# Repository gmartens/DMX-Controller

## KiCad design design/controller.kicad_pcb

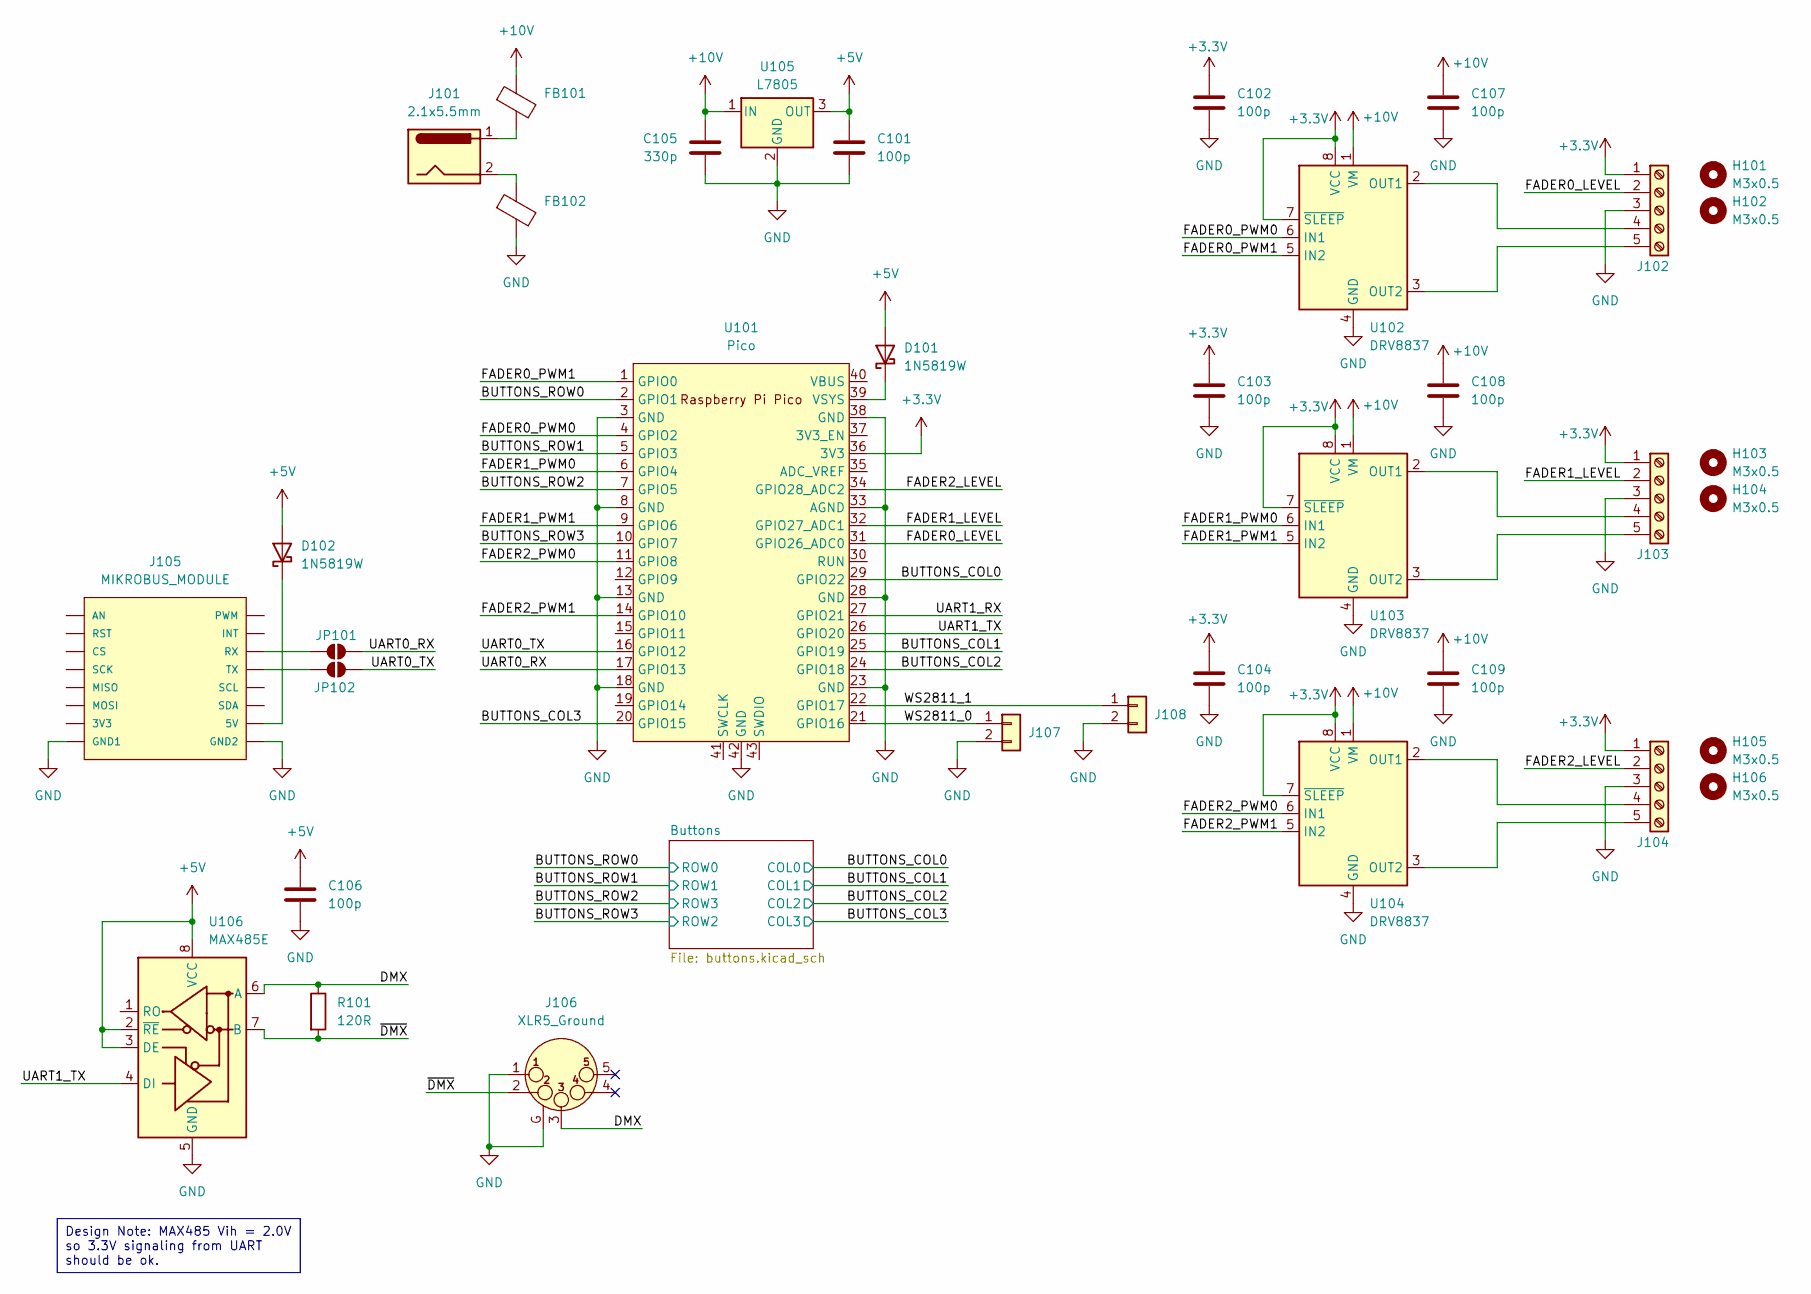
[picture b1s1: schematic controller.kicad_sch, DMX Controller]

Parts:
C101, C102, C103, C104, C106, C107, C108, C109: 100p; C_0805_2012Metric_Pad1.18x1.45mm_HandSolder
C105: 330p; C_0805_2012Metric_Pad1.18x1.45mm_HandSolder
D101, D102: 1N5819W; D_SOD-123F
FB101, FB102: FerriteBead; R_0805_2012Metric_Pad1.20x1.40mm_HandSolder
H101, H102, H103, H104, H105, H106: M3x0.5; MountingHole_3.2mm_M3_DIN965_Pad_TopBottom
J101: 2.1x5.5mm; BarrelJack_CUI_PJ-063AH_Horizontal
J102, J103, J104: Screw_Terminal_01x05; PinHeader_1x05_P2.54mm_Vertical
J105: MIKROBUS_MODULE; MIKROBUS_MODULE_CONN
J106: XLR5_Ground; Jack_XLR_Neutrik_NC5FAH_Horizontal
J107, J108: Conn_01x02; PhoenixContact_MC_1,5_2-G-3.81_1x02_P3.81mm_Horizontal
JP101, JP102: SolderJumper_2_Open; SolderJumper-2_P1.3mm_Open_Pad1.0x1.5mm
R101: 120R; R_0805_2012Metric_Pad1.20x1.40mm_HandSolder
U101: Pico; RPi_Pico_SMD_TH
U102, U103, U104: DRV8837; WSON-8-1EP_2x2mm_P0.5mm_EP0.9x1.6mm
U105: L7805; TO-263-2
U106: MAX485E; SOIC-8_3.9x4.9mm_P1.27mm

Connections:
+3.3V: C102.1, C103.1, C104.1, J102.1, J103.1, J104.1, U101.36 (3V3), U102.7 (~SLEEP), U102.8 (VCC), U103.7 (~SLEEP), U103.8 (VCC), U104.7 (~SLEEP), U104.8 (VCC)
+5V: C101.1, C106.1, D101.2 (A), D102.2 (A), U105.3 (OUT), U106.2 (~RE), U106.3 (DE), U106.8 (VCC)
+10V: C105.1, C107.1, C108.1, C109.1, FB101.1, U102.1 (VM), U103.1 (VM), U104.1 (VM), U105.1 (IN)
/BUTTONS_COL0: U101.29 (GPIO22); also elsewhere on the board
/BUTTONS_COL1: U101.25 (GPIO19); also elsewhere on the board
/BUTTONS_COL2: U101.24 (GPIO18); also elsewhere on the board
/BUTTONS_COL3: U101.20 (GPIO15); also elsewhere on the board
/BUTTONS_ROW0: U101.2 (GPIO1); also elsewhere on the board
/BUTTONS_ROW1: U101.5 (GPIO3); also elsewhere on the board
/BUTTONS_ROW2: U101.7 (GPIO5); also elsewhere on the board
/BUTTONS_ROW3: U101.10 (GPIO7); also elsewhere on the board
/DMX: J106.3, R101.1, U106.6 (A)
/FADER0_LEVEL: J102.2, U101.31 (GPIO26_ADC0)
/FADER0_PWM0: U101.4 (GPIO2), U102.6 (IN1)
/FADER0_PWM1: U101.1 (GPIO0), U102.5 (IN2)
/FADER1_LEVEL: J103.2, U101.32 (GPIO27_ADC1)
/FADER1_PWM0: U101.6 (GPIO4), U103.6 (IN1)
/FADER1_PWM1: U101.9 (GPIO6), U103.5 (IN2)
/FADER2_LEVEL: J104.2, U101.34 (GPIO28_ADC2)
/FADER2_PWM0: U101.11 (GPIO8), U104.6 (IN1)
/FADER2_PWM1: U101.14 (GPIO10), U104.5 (IN2)
/UART0_RX: JP101.2 (B), U101.17 (GPIO13)
/UART0_TX: JP102.2 (B), U101.16 (GPIO12)
/UART1_RX: U101.27 (GPIO21)
/UART1_TX: U101.26 (GPIO20), U106.4 (DI)
/WS2811_0: J107.1, U101.21 (GPIO16)
/WS2811_1: J108.1, U101.22 (GPIO17)
/~DMX: J106.2, R101.2, U106.7 (B)
GND: C101.2, C102.2, C103.2, C104.2, C105.2, C106.2, C107.2, C108.2, C109.2, FB102.2, J102.3, J103.3, J104.3, J105.P8 (GND1), J105.P9 (GND2), J106.1, J106.G, J107.2, J108.2, U101.3 (GND), U101.8 (GND), U101.13 (GND), U101.18 (GND), U101.23 (GND), U101.28 (GND), U101.33 (AGND), U101.38 (GND), U101.42 (GND), U102.4 (GND), U102.9 (GND), U103.4 (GND), U103.9 (GND), U104.4 (GND), U104.9 (GND), U105.2 (GND), U106.5 (GND)
unnamed: D101.1 (K), U101.39 (VSYS)
unnamed: D102.1 (K), J105.P10 (5V)
unnamed: FB101.2, J101.1
unnamed: FB102.1, J101.2
unnamed: J102.4, U102.2 (OUT1)
unnamed: J102.5, U102.3 (OUT2)
unnamed: J103.4, U103.2 (OUT1)
unnamed: J103.5, U103.3 (OUT2)
unnamed: J104.4, U104.2 (OUT1)
unnamed: J104.5, U104.3 (OUT2)
unnamed: J105.P14 (RX), JP101.1 (A)
unnamed: J105.P13 (TX), JP102.1 (A)

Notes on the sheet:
Design Note: MAX485 Vih = 2.0V so 3.3V signaling from UART should be ok.

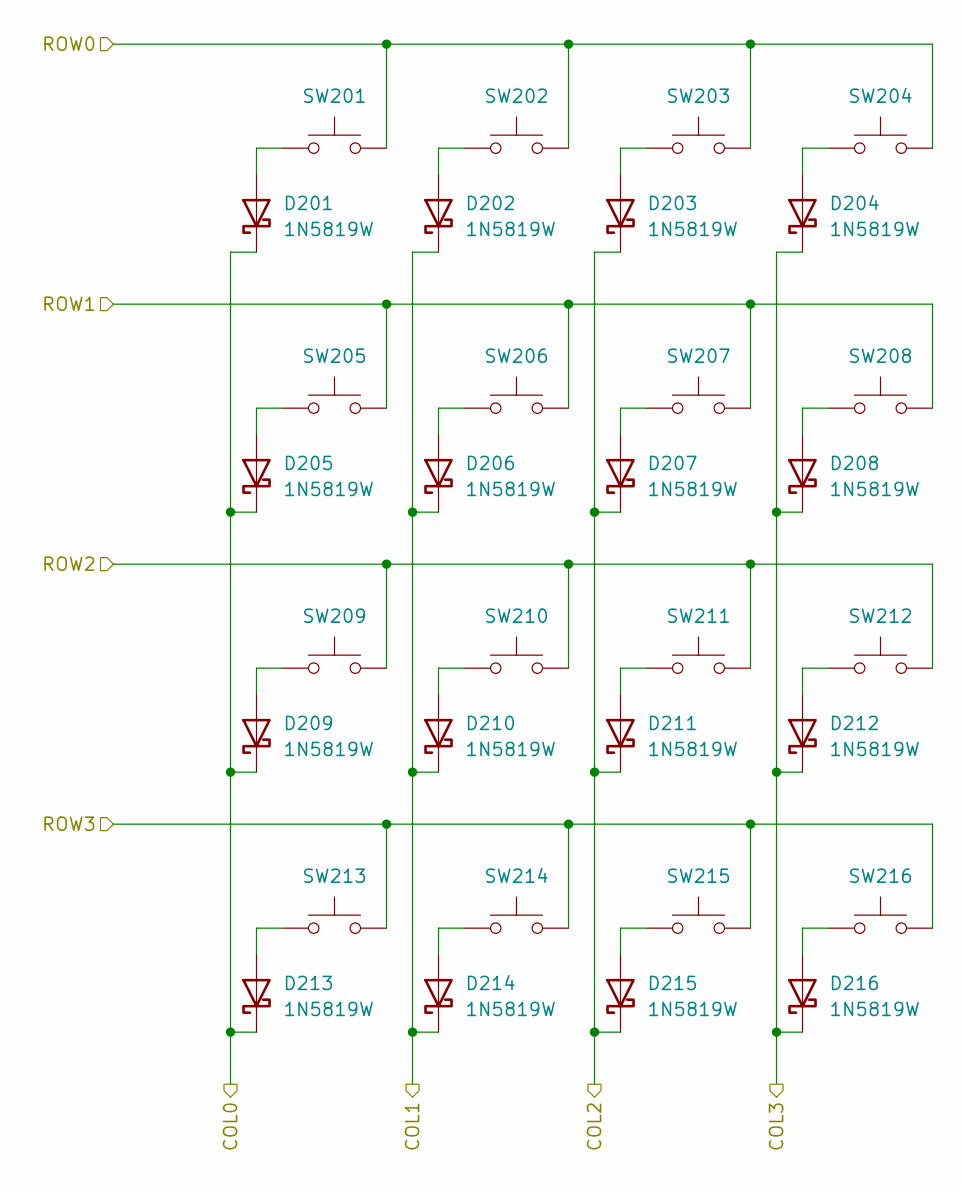
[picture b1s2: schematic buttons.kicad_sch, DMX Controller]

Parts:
D201, D202, D203, D204, D205, D206, D207, D208, D209, D210, D211, D212, D213, D214, D215, D216: 1N5819W; D_SOD-123F
SW201, SW202, SW203, SW204, SW205, SW206, SW207, SW208, SW209, SW210, SW211, SW212, SW213, SW214, SW215, SW216: SW_Push; SW_Cherry_MX_PCB_1.00u

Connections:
/BUTTONS_COL0: D201.1 (K), D205.1 (K), D209.1 (K), D213.1 (K); also elsewhere on the board
/BUTTONS_COL1: D202.1 (K), D206.1 (K), D210.1 (K), D214.1 (K); also elsewhere on the board
/BUTTONS_COL2: D203.1 (K), D207.1 (K), D211.1 (K), D215.1 (K); also elsewhere on the board
/BUTTONS_COL3: D204.1 (K), D208.1 (K), D212.1 (K), D216.1 (K); also elsewhere on the board
/BUTTONS_ROW0: SW201.2, SW202.2, SW203.2, SW204.2; also elsewhere on the board
/BUTTONS_ROW1: SW205.2, SW206.2, SW207.2, SW208.2; also elsewhere on the board
/BUTTONS_ROW2: SW213.2, SW214.2, SW215.2, SW216.2; also elsewhere on the board
/BUTTONS_ROW3: SW209.2, SW210.2, SW211.2, SW212.2; also elsewhere on the board
unnamed: D201.2 (A), SW201.1
unnamed: D202.2 (A), SW202.1
unnamed: D203.2 (A), SW203.1
unnamed: D204.2 (A), SW204.1
unnamed: D205.2 (A), SW205.1
unnamed: D206.2 (A), SW206.1
unnamed: D207.2 (A), SW207.1
unnamed: D208.2 (A), SW208.1
unnamed: D209.2 (A), SW209.1
unnamed: D210.2 (A), SW210.1
unnamed: D211.2 (A), SW211.1
unnamed: D212.2 (A), SW212.1
unnamed: D213.2 (A), SW213.1
unnamed: D214.2 (A), SW214.1
unnamed: D215.2 (A), SW215.1
unnamed: D216.2 (A), SW216.1

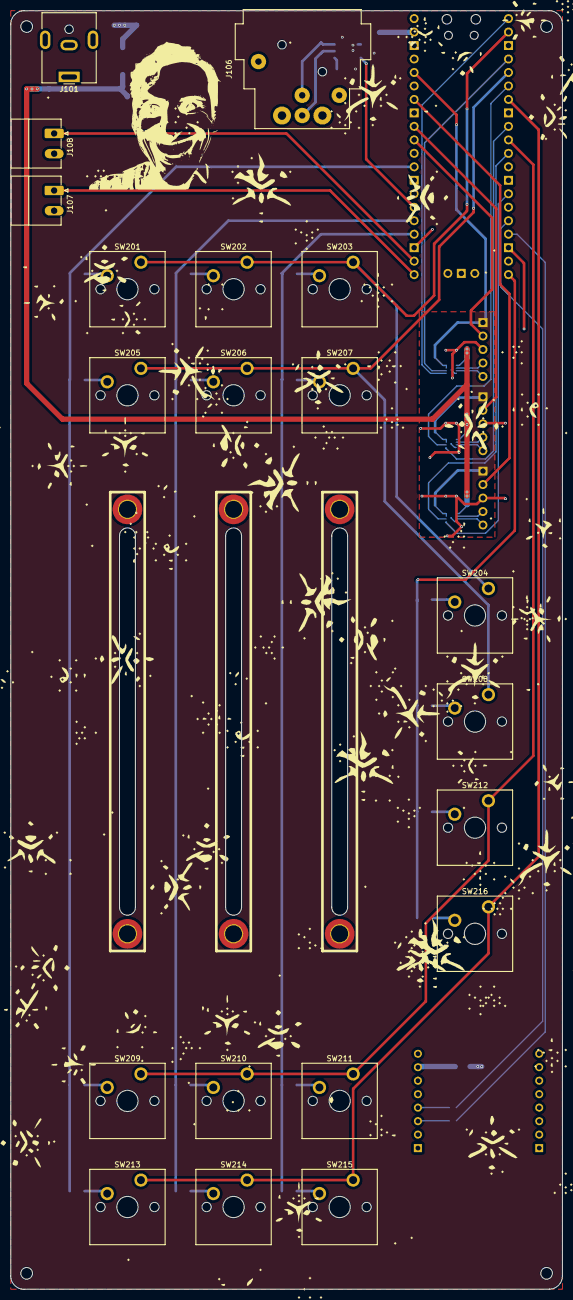
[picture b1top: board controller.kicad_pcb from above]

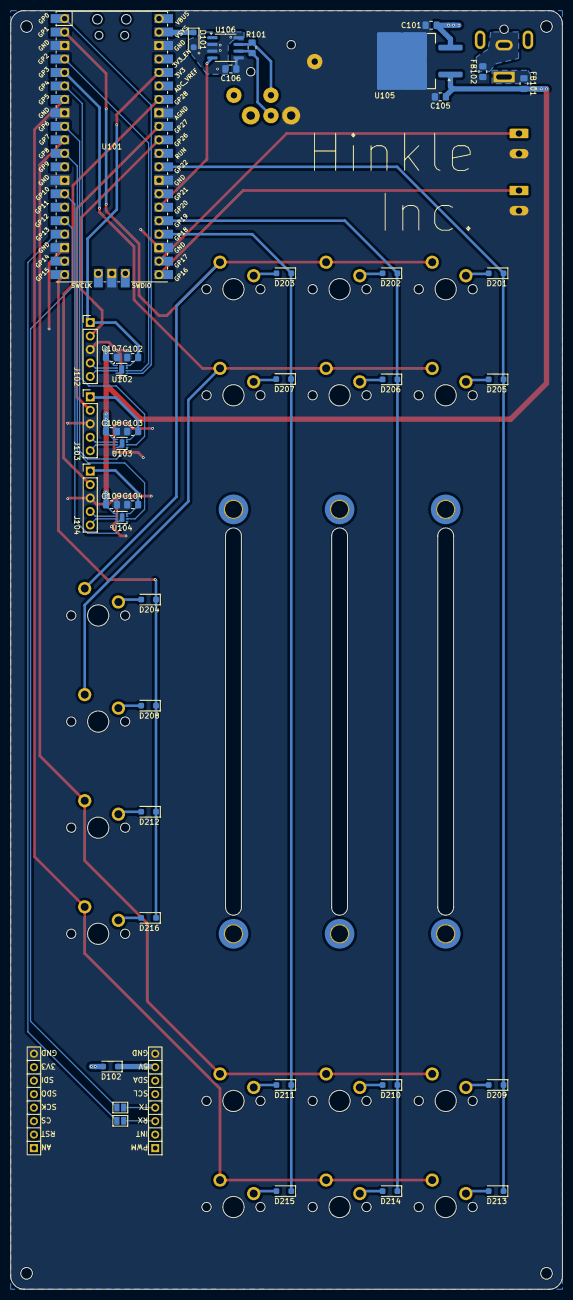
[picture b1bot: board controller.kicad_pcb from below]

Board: 2 copper layers, 104.0 x 241.0 mm, 68 parts (42 on the bottom side), 56 nets.

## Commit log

2024-11-18 init commit
2024-11-18 start layout
2024-11-18 routing
2024-11-20 final design
2024-12-01 create pico and avr projects
2024-12-02 remove clangd caching
2024-12-02 add dmx
2024-12-04 add motor control
2024-12-04 add all 3 bluetooth chars
2024-12-04 lots of stuff, refactoring, adding dmx to faders
